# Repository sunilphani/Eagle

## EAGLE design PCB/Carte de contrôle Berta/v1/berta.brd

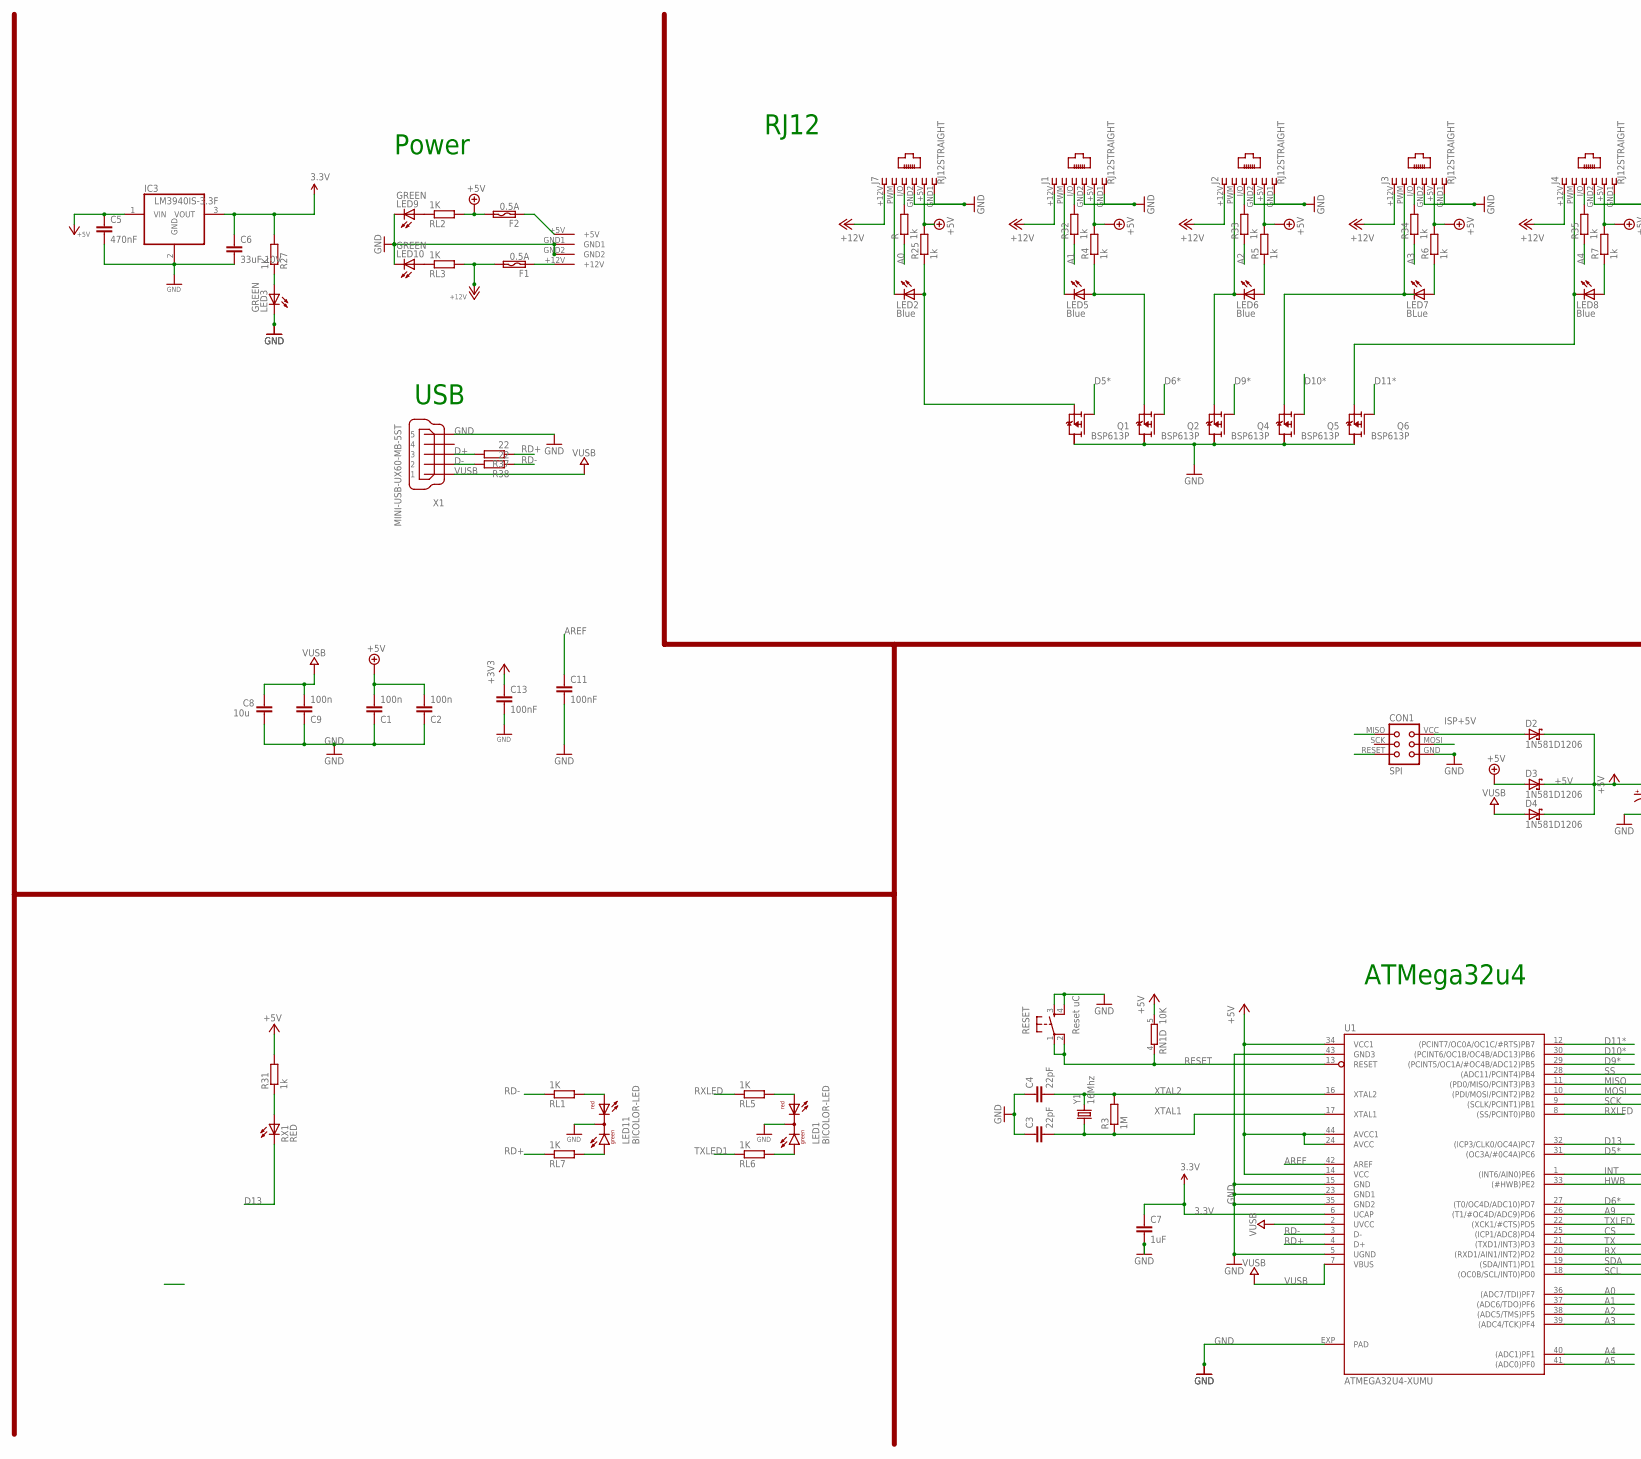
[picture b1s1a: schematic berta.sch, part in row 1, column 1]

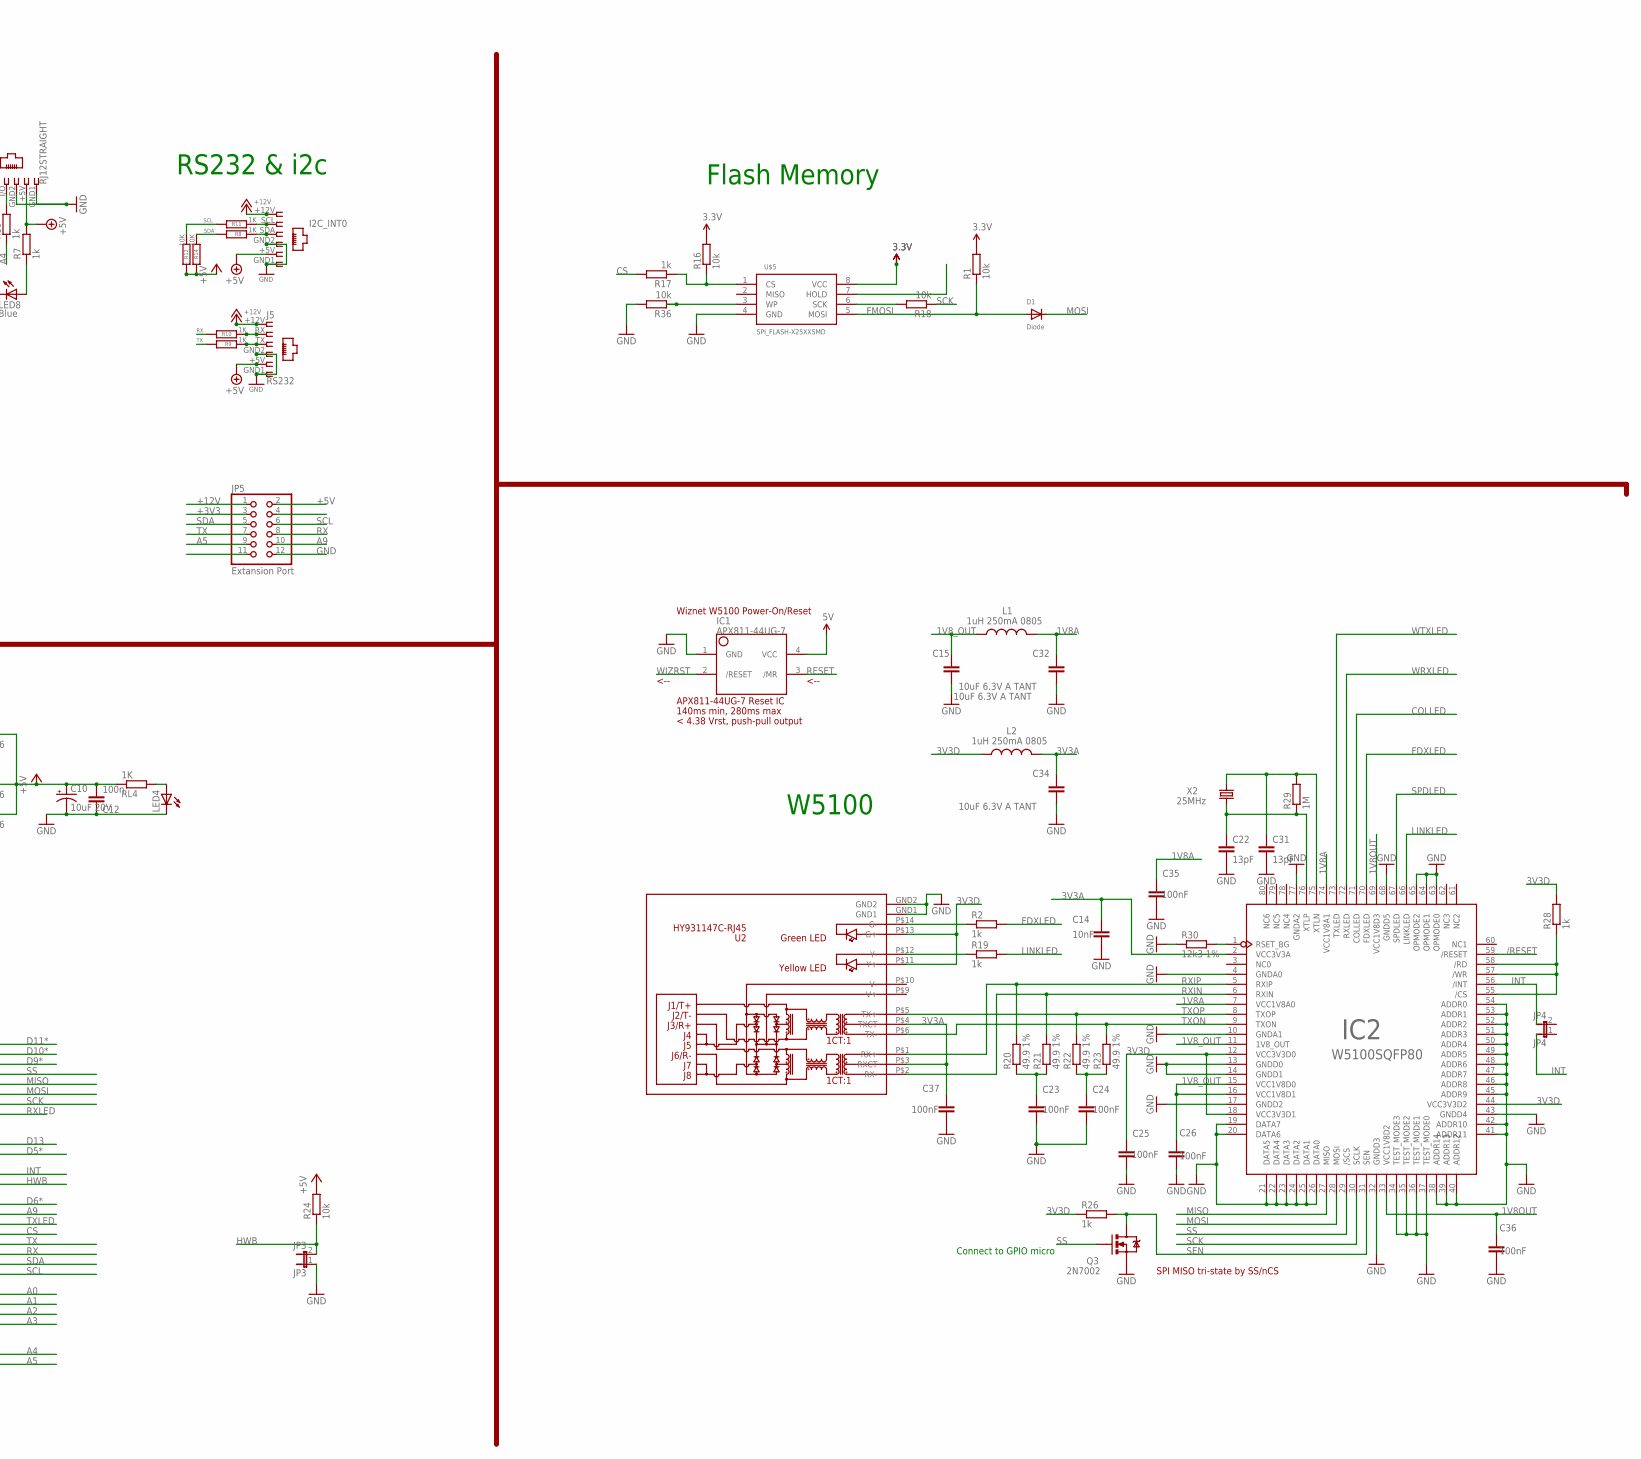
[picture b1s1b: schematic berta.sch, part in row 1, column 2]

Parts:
C1, C2, C9: 100n; C0805
C3, C4: 22pF; C0805
C5: 470nF; C0805
C6: 33uF 10V; C050-045X075
C7: 1uF; C0805
C8: 10u; C0805
C10: 10uF 20V; EIA3216-KIT
C11, C13, C23, C24, C25, C26, C35, C36, C37: 100nF; C0805
C12: 100n; C0603-ROUND
C14: 10nF; C0805
C15, C32, C34: 10uF 6.3V A TANT; C0805
C22, C31: 13pF; C0805
CON1: SPI; TINYISP
D1: Diode; SMADIODE
D2, D3, D4: 1N581D1206; LED-1206
F1, F2: 0.5A; C1812
I2C_INT0: I2C; RJ12-STRAIGHT-I2C
IC1: APX811-44UG-7; SOT143-R
IC2: W5100SQFP80; SQFP80
IC3: LM3940IS-3.3F; DD-3
J1, J2, J3, J4, J7: RJ12STRAIGHT; RJ12-STRAIGHT
J5: RS232; RJ12-STRAIGHT-RS232
JP3: JP3; 1X02
JP4: JP4; 1X02
JP5: Extansion Port; 2X06
L1, L2: 1uH 250mA 0805; L2012C
LED1, LED11: BICOLOR-LED; BICOLOR-3MM
LED2, LED5, LED6, LED8: Blue; SML0805
LED3, LED9, LED10: GREEN; SML0805
LED4: LED3MM
LED7: BLue; SML0805
Q1, Q2, Q4, Q5, Q6: BSP613P; PG-SOT-223
Q3: 2N7002; SOT23-3
R, R4, R5, R6, R7, R17, R25, R32, R33, R34, R35: 1k; M0805
R1, R16, R18, R36: 10k; M0805
R2, R19, R26, R28: 1k; R0805W
R3, R29: 1M; R0805W
R8, R9, R10, R11, R27: 1K; M1206
R12, R14: 10K; M1206
R20, R21, R22, R23: 49.9 1%; R0805W
R24: 10k; R0805W
R30: 12k3 1%; R0805W
R31: 1k; R0805
R37, R38: 22; M1206
RESET: Reset uC; TACTILE_SWITCH_SMD
RL1, RL4, RL5, RL6, RL7: 1K; M1206
RL2, RL3: 1K; R0805W
RN1: 10K; CAY16
RX1: RED; SML0805
U1: ATMEGA32U4-XUMU; QFN44ML7X7
U2: HY931147C-RJ45; HY931147C
U$5: SPI_FLASH-X25XXSMD; SO08
U$6: KPJX-4S-S
X1: MINI-USB-UX60-MB-5ST; UX60-MB-5ST
X2: 25MHz; HC49U-V
Y1: 16Mhz; HC49US

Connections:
1V8A: C32.1, C35.1, IC2.7 (VCC1V8A0), IC2.74 (VCC1V8A1), L1.2
1V8OUT: C36.1, IC2.33 (VCC1V8D2), IC2.69 (VCC1V8D3)
1V8_OUT: C15.1, C26.1, IC2.11 (1V8_OUT), IC2.15 (VCC1V8D0), IC2.16 (VCC1V8D1), L1.1
3.3V: C6.1, C7.1, IC3.3 (VOUT), R1.2, R16.2, R27.2, U1.6 (UCAP), U$5.8 (VCC)
3V3A: C14.1, C34.1, C37.1, IC2.2 (VCC3V3A), L2.2, U2.P$3 (RXCT), U2.P$4 (TXCT)
3V3D: C25.1, IC2.12 (VCC3V3D0), IC2.18 (VCC3V3D1), IC2.44 (VCC3V3D2), L2.1, R26.1, R28.2, U2.P$11 (Y+), U2.P$13 (G+)
5V: IC1.4 (VCC)
+3V3: C13.1
+5V: C1.2, C2.2, C5.1, C10.A (+), C12.2, D2.C, D3.A, D3.C, D4.C, F2.2, I2C_INT0.+5V (5), IC3.1 (VIN), J1.+5V (5), J2.+5V (5), J3.+5V (5), J4.+5V (5), J5.+5V (5), J7.+5V (5), JP5.2, R4.2, R5.2, R6.2, R7.2, R12.2, R14.2, R24.2, R25.2, R31.2, RL2.2, RL4.1, RN1.5 (2), U1.14 (VCC), U1.24 (AVCC), U1.34 (VCC1), U1.44 (AVCC1)
+12V: F1.2, I2C_INT0.+12V (1), J1.+12V (1), J2.+12V (1), J3.+12V (1), J4.+12V (1), J5.+12V (1), J7.+12V (1), RL3.2
/RESET: IC2.59 (/RESET)
A0: R.1, U1.36 ((ADC7/TDI)PF7)
A1: R32.1, U1.37 ((ADC6/TDO)PF6)
A2: R33.1, U1.38 ((ADC5/TMS)PF5)
A3: R34.1, U1.39 ((ADC4/TCK)PF4)
A4: R35.1, U1.40 ((ADC1)PF1)
A5: JP5.9, U1.41 ((ADC0)PF0)
A9: JP5.10, U1.26 ((T1/#OC4D/ADC9)PD6)
AREF: C11.1, U1.42 (AREF)
COLLED: IC2.71 (COLLED)
CS: R17.2, U1.25 ((ICP1/ADC8)PD4)
D2B4: I2C_INT0.SDA (3), R8.1
D2B5: J5.TX (3), R9.1
D5*: Q1.1 (G), U1.31 ((OC3A/#0C4A)PC6)
D6*: Q2.1 (G), U1.27 ((T0/OC4D/ADC10)PD7)
D9*: Q4.1 (G), U1.29 ((PCINT5/OC1A/#OC4B/ADC12)PB5)
D10*: Q5.1 (G), U1.30 ((PCINT6/OC1B/OC4B/ADC13)PB6)
D11*: Q6.1 (G), U1.12 ((PCINT7/OC0A/OC1C/#RTS)PB7)
D13: RX1.C, U1.32 ((ICP3/CLK0/OC4A)PC7)
D+: R37.2, X1.3
D-: R38.2, X1.2
FDXLED: IC2.70 (FDXLED), R2.2
FMOSI: D1.A, R1.1, U$5.5 (MOSI)
GND: C1.1, C2.1, C3.1, C4.1, C5.2, C6.2, C7.2, C8.2, C9.1, C10.C (-), C11.2, C12.1, C13.2, C14.2, C15.2, C22.2, C23.2, C24.2, C25.2, C26.2, C31.2, C32.2, C34.2, C35.2, C36.2, C37.2, CON1.GND, I2C_INT0.GND1 (6), I2C_INT0.GND2 (4), IC1.1 (GND), IC2.4 (GNDA0), IC2.10 (GNDA1), IC2.13 (GNDD0), IC2.14 (GNDD1), IC2.17 (GNDD2), IC2.19 (DATA7), IC2.20 (DATA6), IC2.21 (DATA5), IC2.22 (DATA4), IC2.23 (DATA3), IC2.24 (DATA2), IC2.25 (DATA1), IC2.26 (DATA0), IC2.32 (GNDD3), IC2.34 (TEST_MODE3), IC2.35 (TEST_MODE2), IC2.36 (TEST_MODE1), IC2.37 (TEST_MODE0), IC2.38 (ADDR14), IC2.39 (ADDR13), IC2.40 (ADDR12), IC2.41 (ADDR11), IC2.42 (ADDR10), IC2.43 (GNDD4), IC2.45 (ADDR9), IC2.46 (ADDR8), IC2.47 (ADDR7), IC2.48 (ADDR6), IC2.49 (ADDR5), IC2.50 (ADDR4), IC2.51 (ADDR3), IC2.52 (ADDR2), IC2.53 (ADDR1), IC2.54 (ADDR0), IC2.63 (OPMODE0), IC2.64 (OPMODE1), IC2.65 (OPMODE2), IC2.68 (GNDD5), IC2.77 (GNDA2), IC3.2 (GND), J1.GND1 (6), J1.GND2 (4), J2.GND1 (6), J2.GND2 (4), J3.GND1 (6), J3.GND2 (4), J4.GND1 (6), J4.GND2 (4), J5.GND1 (6), J5.GND2 (4), J7.GND1 (6), J7.GND2 (4), JP3.1, JP5.12, LED1.2 (C), LED3.C, LED4.K (C), LED9.C, LED10.C, LED11.2 (C), Q1.2 (D), Q2.2 (D), Q3.2 (S), Q4.2 (D), Q5.2 (D), Q6.2 (D), R30.1, R36.2, RESET.3, RESET.4, U1.5 (UGND), U1.15 (GND), U1.23 (GND1), U1.35 (GND2), U1.43 (GND3), U1.EXP (PAD), U2.GND1, U2.GND2, U$5.4 (GND), U$6.GND1, U$6.GND2, X1.5
HWB: JP3.2, R24.1, U1.33 ((#HWB)PE2)
INT: IC2.56 (/INT), U1.1 ((INT6/AIN0)PE6)
ISP+5V: CON1.VCC, D2.A
LINKLED: IC2.66 (LINKLED), R19.2
MISO: CON1.MISO, IC2.27 (MISO), U1.11 ((PD0/MISO/PCINT3)PB3)
MOSI: CON1.MOSI, D1.C, IC2.28 (MOSI), U1.10 ((PDI/MOSI/PCINT2)PB2)
unnamed: J2.PWM (2), LED6.C, Q4.3 (S)
unnamed: J1.I/O (3), R32.2
unnamed: R31.1, RX1.A
unnamed: LED5.A, Q2.3 (S), R4.1
unnamed: J3.PWM (2), LED7.C, Q5.3 (S)
unnamed: J2.I/O (3), R33.2
unnamed: LED11.3 (AR), RL1.2
unnamed: C24.1, R22.1, R23.1
unnamed: R16.1, R17.1, U$5.1 (CS)
unnamed: R36.1, U$5.3 (WP)
unnamed: LED4.A, RL4.2
unnamed: LED1.3 (AR), RL5.2
unnamed: LED11.1 (AG), RL7.2
unnamed: LED1.1 (AG), RL6.2
unnamed: J7.I/O (3), R.2
unnamed: J4.PWM (2), LED8.C, Q6.3 (S)
unnamed: LED3.A, R27.1
unnamed: LED2.A, Q1.3 (S), R25.1
unnamed: LED6.A, R5.1
unnamed: R18.2, U$5.6 (SCK)
unnamed: IC2.55 (/CS), IC2.57 (/WR), IC2.58 (/RD), R28.1
unnamed: J1.PWM (2), LED5.C
unnamed: J3.I/O (3), R34.2
unnamed: LED7.A, R6.1
unnamed: J4.I/O (3), R35.2
unnamed: LED8.A, R7.1
unnamed: J7.PWM (2), LED2.C
unnamed: F2.1, U$6.+5V
unnamed: F1.1, U$6.+12V
unnamed: R2.1, U2.P$14 (G-)
unnamed: J5.RX (2), R10.1
unnamed: I2C_INT0.SCL (2), R11.1
unnamed: LED10.A, RL3.1
unnamed: LED9.A, RL2.1
unnamed: C23.1, R20.1, R21.1
unnamed: IC2.1 (RSET_BG), R30.2
unnamed: R19.1, U2.P$12 (Y-)
RD+: R37.1, RL7.1, U1.4 (D+)
RD-: R38.1, RL1.1, U1.3 (D-)
RESET: CON1.RESET, IC1.3 (/MR), RESET.1, RESET.2, RN1.4 (1), U1.13 (RESET)
RX: JP5.8, R10.2, U1.20 ((RXD1/AIN1/INT2)PD2)
RXIN: IC2.6 (RXIN), R21.2, U2.P$2 (RX-)
RXIP: IC2.5 (RXIP), R20.2, U2.P$1 (RX+)
RXLED: RL5.1, U1.8 ((SS/PCINT0)PB0)
SCK: IC2.30 (SCLK), R18.1, U1.9 ((SCLK/PCINT1)PB1)
SCL: JP5.6, R11.2, R12.1, U1.18 ((OC0B/SCL/INT0)PD0)
SDA: JP5.5, R8.2, R14.1, U1.19 ((SDA/INT1)PD1)
SEN: IC2.31 (SEN), Q3.3 (D), R26.2
SPDLED: IC2.67 (SPDLED)
SS: IC2.29 (/SCS), Q3.1 (G), U1.28 ((ADC11/PCINT4)PB4)
TX: JP5.7, R9.2, U1.21 ((TXD1/INT3)PD3)
TXLED: U1.22 ((XCK1/#CTS)PD5)
TXLED1: RL6.1
TXON: IC2.9 (TXON), R23.2, U2.P$6 (TX-)
TXOP: IC2.8 (TXOP), R22.2, U2.P$5 (TX+)
VUSB: C8.1, C9.2, D4.A, U1.2 (UVCC), U1.7 (VBUS), X1.1
WIZRST: IC1.2 (/RESET)
WRXLED: IC2.72 (RXLED)
WTXLED: IC2.73 (TXLED)
XTAL1: C3.2, R3.1, U1.17 (XTAL1), Y1.1
XTAL2: C4.2, R3.2, U1.16 (XTAL2), Y1.2
XTLN: C31.1, IC2.75 (XTLN), R29.2, X2.2
XTLP: C22.1, IC2.76 (XTLP), R29.1, X2.1

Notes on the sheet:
Flash Memory
RJ12
ATMega32u4
W5100
USB
Power
RS232 & i2c
SPI MISO tri-state by SS/nCS
Connect to GPIO micro
APX811-44UG-7 Reset IC
140ms min, 280ms max
Wiznet W5100 Power-On/Reset
< 4.38 Vrst, push-pull output
<--

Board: 2 copper layers, 119 parts (0 on the bottom side), 93 nets, no tracks yet.

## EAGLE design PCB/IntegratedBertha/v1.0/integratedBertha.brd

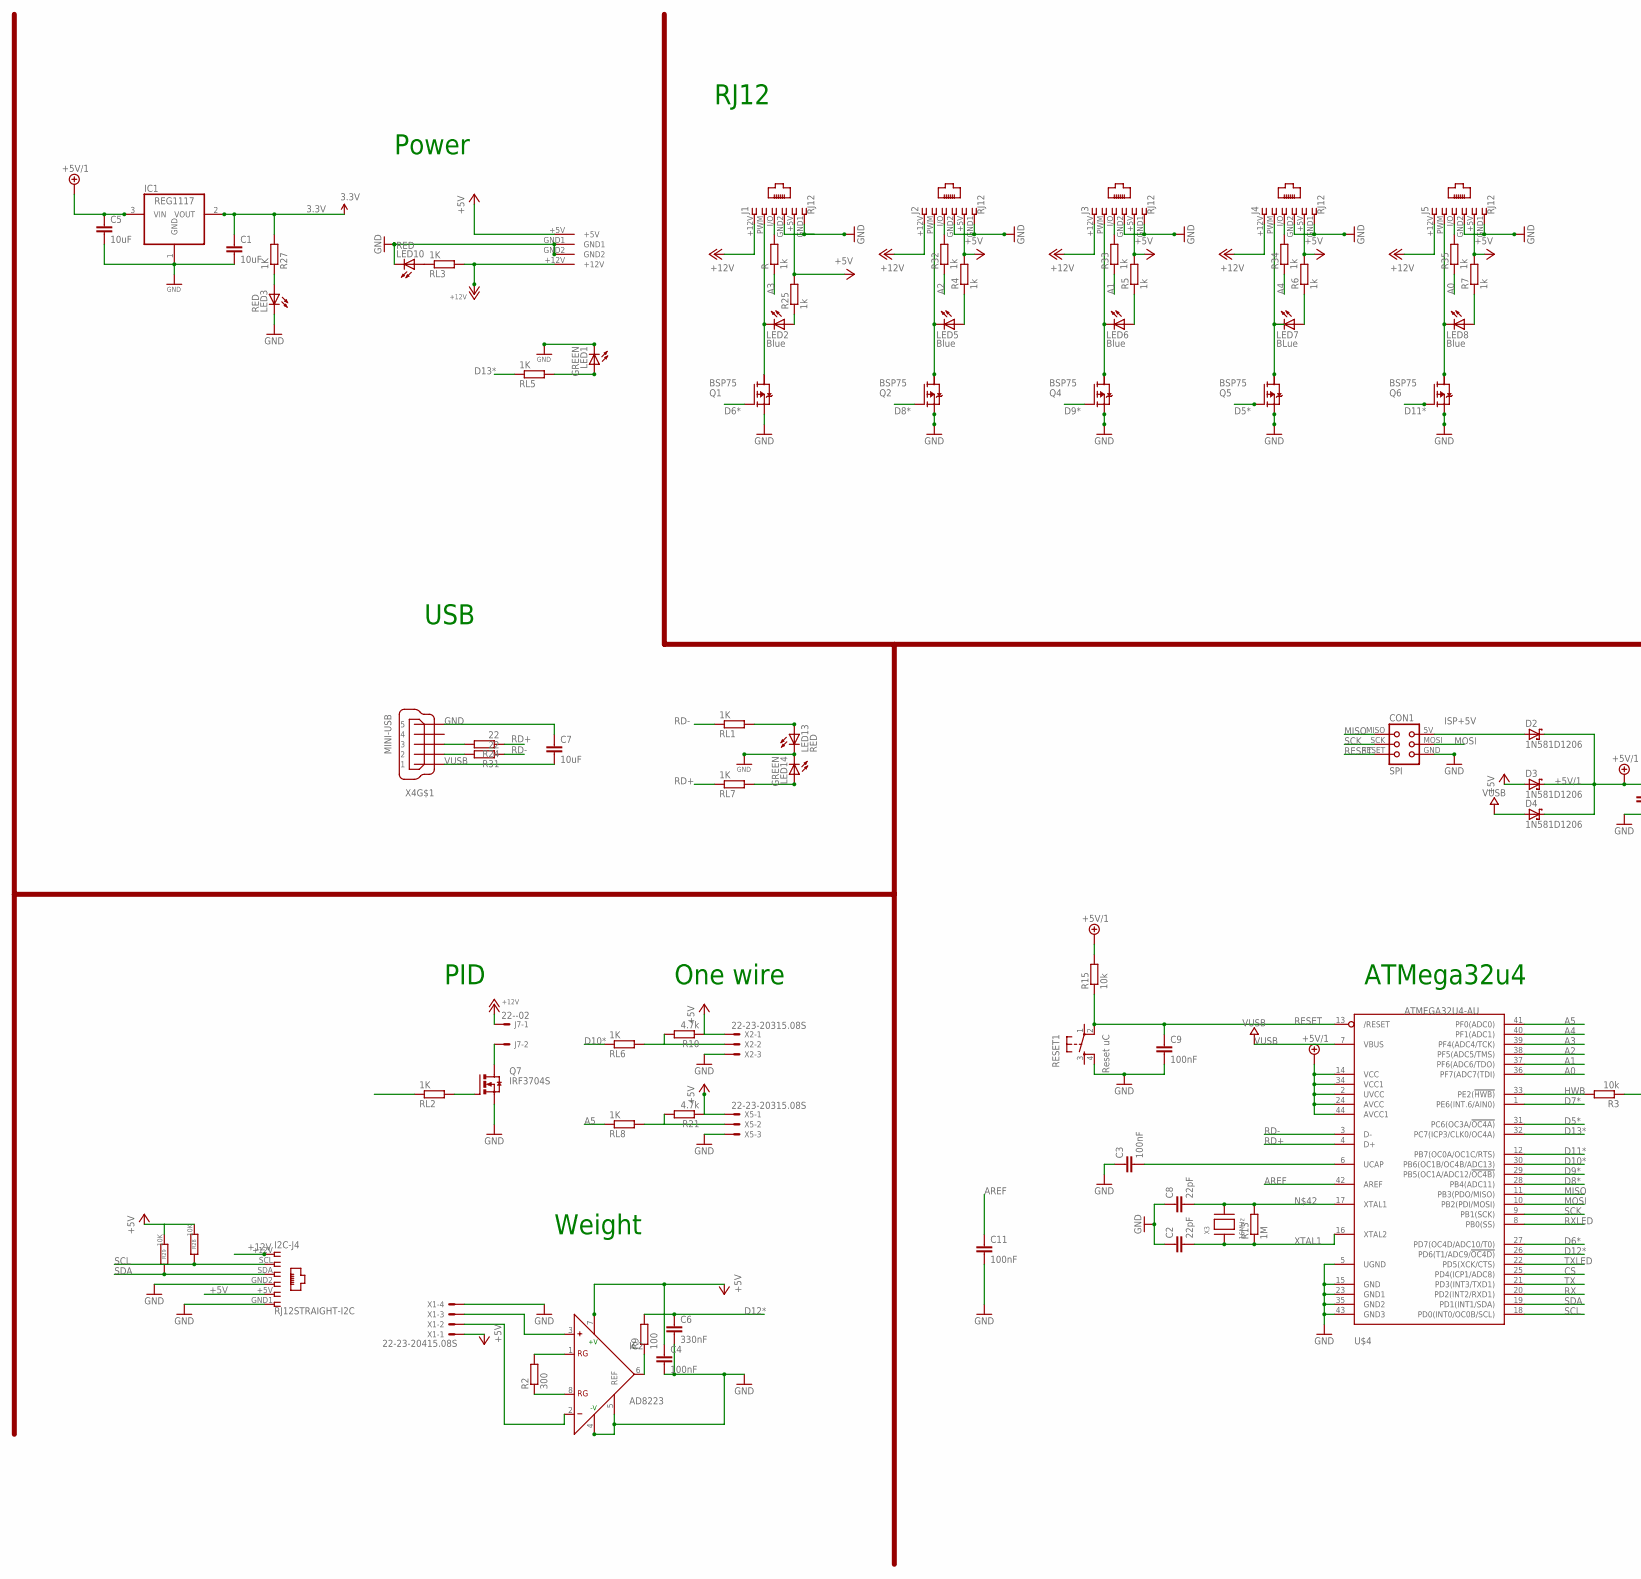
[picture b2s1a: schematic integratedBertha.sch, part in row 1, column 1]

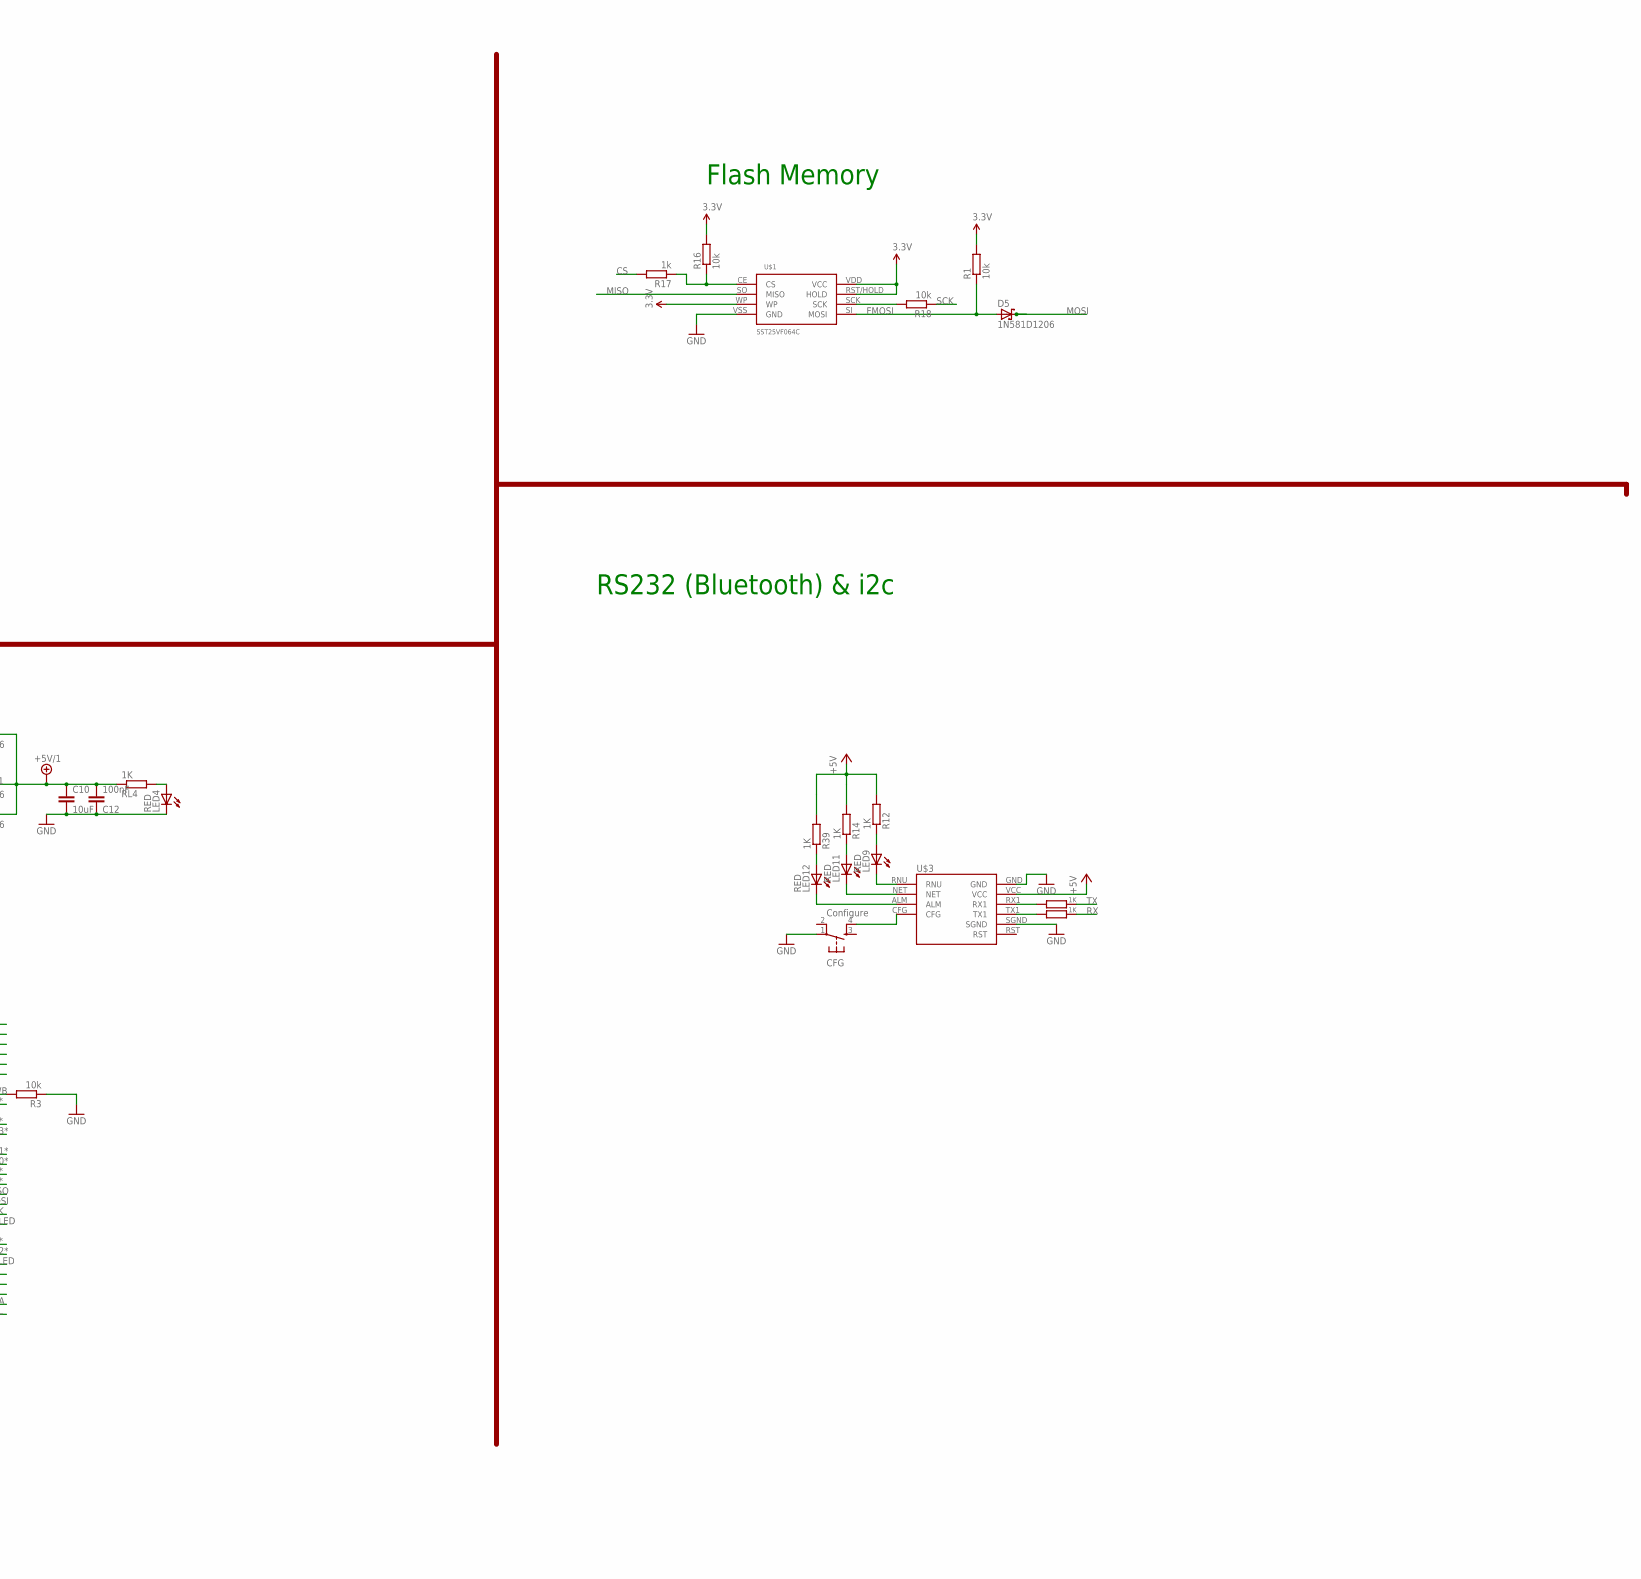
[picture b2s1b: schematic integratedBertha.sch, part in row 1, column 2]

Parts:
C1, C5, C7, C10: 10uF; C1206
C2, C8: 22pF; C1206
C3, C4, C9, C11, C12: 100nF; C1206
C6: 330nF; C1206
CFG: Configure; TACTILE_SWITCH_SMD
CON1: SPI; TC2030-MCP-NL
D2, D3, D4, D5: 1N581D1206; LED-1206
I2C-J4: RJ12STRAIGHT-I2C; RJ12-STRAIGHT-I2C
IC1: REG1117; SOT223
IC2: AD8223; SO8
J1, J2, J3, J4, J5: RJ12; RJ12-STRAIGHT
J7: 22--02; 2-PIN-5.08S
LED1, LED14: GREEN; CHIPLED_1206
LED2, LED5, LED6, LED8: Blue; CHIPLED_1206
LED3, LED4, LED9, LED10, LED11, LED12, LED13: RED; CHIPLED_1206
LED7: BLue; CHIPLED_1206
Q1, Q2, Q4, Q5, Q6: BSP75; PG-SOT-223
Q7: IRF3704S; D2PACK
R, R4, R5, R6, R7, R17, R25, R32, R33, R34, R35: 1k; R0805
R1, R16, R18: 10k; R0805
R2: 300; R1206
R3, R15: 10k; M0805
R8, R11, R12, R14, R27, R39: 1K; R0805
R9: 100; R1206
R10, R21: 4.7k; R1206
R13: 1M; R1206
R24, R31: 22; M1206
R28, R29: 10K; M0805
RESET1: Reset uC; TACTILE_SWITCH_SMD
RL1, RL2, RL3, RL4, RL5, RL6, RL7, RL8: 1K; R0805
U$1: SST25VF064C; SOIC_8-LEAD
U$3: SZ05-ZIGBEE
U$4: ATMEGA32U4-AU; TQFP44
U$6: KPJX-4S-S
X1: 22-23-20415.08S; 4-PIN-5.08S
X2, X5: 22-23-20315.08S; 3-PIN-5.08S
X3: 16MHz; NX6035
X4: MINI-USB; 32005-201

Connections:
3.3V: C1.1, IC1.2 (VOUT), R1.2, R16.2, R27.2, U$1.RST/HOLD (HOLD), U$1.VDD (VCC), U$1.WP
+5V: C4.1, D3.A, I2C-J4.+5V (5), IC2.7 (+V), J1.+5V (5), J2.+5V (5), J3.+5V (5), J4.+5V (5), J5.+5V (5), R4.2, R5.2, R6.2, R7.2, R10.1, R12.2, R14.2, R21.1, R25.2, R28.1, R29.1, R39.2, U$3.VCC, U$6.+5V, X1.1, X2.1, X5.1
+5V/1: C5.1, C10.1, C12.2, D2.C, D3.C, D4.C, IC1.3 (VIN), R15.2, RL4.1, U$4.2 (UVCC), U$4.14 (VCC), U$4.24 (AVCC), U$4.34 (VCC1), U$4.44 (AVCC1)
+12V: I2C-J4.+12V (1), J1.+12V (1), J2.+12V (1), J3.+12V (1), J4.+12V (1), J5.+12V (1), J7.1, RL3.2, U$6.+12V
A0: R35.1, U$4.36 (PF7(ADC7(TDI))
A1: R33.1, U$4.37 (PF6(ADC6/TDO))
A2: R32.1, U$4.38 (PF5(ADC5/TMS))
A3: R.1, U$4.39 (PF4(ADC4/TCK))
A4: R34.1, U$4.40 (PF1(ADC1))
A5: RL8.1, U$4.41 (PF0(ADC0))
AREF: C11.1, U$4.42 (AREF)
CS: R17.2, U$4.25 (PD4(ICP1/ADC8))
D5*: Q5.1 (G), U$4.31 (PC6(OC3A/!OC4A))
D6*: Q1.1 (G), U$4.27 (PD7(OC4D/ADC10/T0))
D7*: RL2.1, U$4.1 (PE6(INT.6/AIN0))
D8*: Q2.1 (G), U$4.28 (PB4(ADC11))
D9*: Q4.1 (G), U$4.29 (PB5(OC1A/ADC12/!OC4B))
D10*: RL6.1, U$4.30 (PB6(OC1B/OC4B/ADC13))
D11*: Q6.1 (G), U$4.12 (PB7(OC0A/OC1C/RTS))
D12*: C6.1, R9.2, U$4.26 (PD6(T1/ADC9/!OC4D))
D13*: RL5.1, U$4.32 (PC7(ICP3/CLK0/OC4A))
D+USB: R24.2, X4.3
D-USB: R31.2, X4.2
DIFF+: IC2.3 (+), X1.3
DIFF-: IC2.2 (-), X1.2
FMOSI: D5.A, R1.1, U$1.SI (MOSI)
GND: C1.2, C2.1, C3.1, C4.2, C5.2, C6.2, C7.1, C8.1, C9.2, C10.2, C11.2, C12.1, CFG.1, CON1.GND, I2C-J4.GND1 (6), I2C-J4.GND2 (4), IC1.1 (GND), IC2.4 (-V), IC2.5 (REF), J1.GND1 (6), J1.GND2 (4), J2.GND1 (6), J2.GND2 (4), J3.GND1 (6), J3.GND2 (4), J4.GND1 (6), J4.GND2 (4), J5.GND1 (6), J5.GND2 (4), LED1.C, LED3.C, LED4.C, LED10.C, LED13.C, LED14.C, Q1.3 (S), Q2.3 (S), Q4.3 (S), Q5.3 (S), Q6.3 (S), Q7.3 (S), R3.1, RESET1.4, U$1.VSS (GND), U$3.GND, U$3.SGND, U$4.5 (UGND), U$4.15 (GND), U$4.23 (GND1), U$4.35 (GND2), U$4.43 (GND3), U$6.GND1, U$6.GND2, X1.4, X2.3, X4.5, X5.3
GND1: LED9.C, U$3.RNU
GND2: LED11.C, U$3.NET
GND3: LED12.C, U$3.ALM
HWB: R3.2, U$4.33 (PE2(!HWB))
ISP+5V: CON1.5V (VCC), D2.A
MISO: CON1.MISO, U$1.SO (MISO), U$4.11 (PB3(PDO/MISO))
MOSI: CON1.MOSI, D5.C, U$4.10 (PB2(PDI/MOSI))
unnamed: J3.PWM (2), LED6.C, Q4.2 (D)
unnamed: J2.I/O (3), R32.2
unnamed: LED1.A, RL5.2
unnamed: LED5.A, R4.1
unnamed: J4.PWM (2), LED7.C, Q5.2 (D)
unnamed: Q7.1 (G), RL2.2
unnamed: J3.I/O (3), R33.2
unnamed: LED13.A, RL1.2
unnamed: R21.2, RL8.2, X5.2
unnamed: R16.1, R17.1, U$1.CE (CS)
unnamed: R11.2, U$3.RX1
unnamed: LED4.A, RL4.2
unnamed: IC2.1 (RG), R2.2
unnamed: LED14.A, RL7.2
unnamed: IC2.8 (RG), R2.1
unnamed: C3.2, U$4.6 (UCAP)
unnamed: LED2.A, R25.1
unnamed: J1.I/O (3), R.2
unnamed: J5.PWM (2), LED8.C, Q6.2 (D)
unnamed: LED3.A, R27.1
unnamed: R10.2, RL6.2, X2.2
unnamed: LED6.A, R5.1
unnamed: R18.2, U$1.SCK
unnamed: R8.2, U$3.TX1
unnamed: LED9.A, R12.1
unnamed: LED11.A, R14.1
unnamed: LED12.A, R39.1
unnamed: J2.PWM (2), LED5.C, Q2.2 (D)
unnamed: J4.I/O (3), R34.2
unnamed: LED7.A, R6.1
unnamed: J5.I/O (3), R35.2
unnamed: LED8.A, R7.1
unnamed: J1.PWM (2), LED2.C, Q1.2 (D)
unnamed: CFG.4, U$3.CFG
unnamed: J7.2, Q7.2 (D)
unnamed: IC2.6 (OUT), R9.1
unnamed: C8.2, R13.2, U$4.17 (XTAL1), X3.P$2
unnamed: LED10.A, RL3.1
RD+: R24.1, RL7.1, U$4.4 (D+)
RD-: R31.1, RL1.1, U$4.3 (D-)
RESET: C9.1, CON1.RESET, R15.1, RESET1.2, U$4.13 (/RESET)
RX: R8.1, U$4.20 (PD2(INT2/RXD1))
RXLED: U$4.8 (PB0(SS))
SCK: CON1.SCK, R18.1, U$4.9 (PB1(SCK))
SCL: I2C-J4.SCL (2), R28.2, U$4.18 (PD0(INT0/OC0B/SCL))
SDA: I2C-J4.SDA (3), R29.2, U$4.19 (PD1(INT1/SDA))
TX: R11.1, U$4.21 (PD3(INT3/TXD1))
TXLED: U$4.22 (PD5(XCK/CTS))
VUSB: C7.2, D4.A, U$4.7 (VBUS), X4.1
XTAL1: C2.2, R13.1, U$4.16 (XTAL2), X3.P$1

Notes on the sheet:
Flash Memory
RJ12
ATMega32u4
USB
Power
RS232 (Bluetooth) & i2c
PID
One wire
Weight

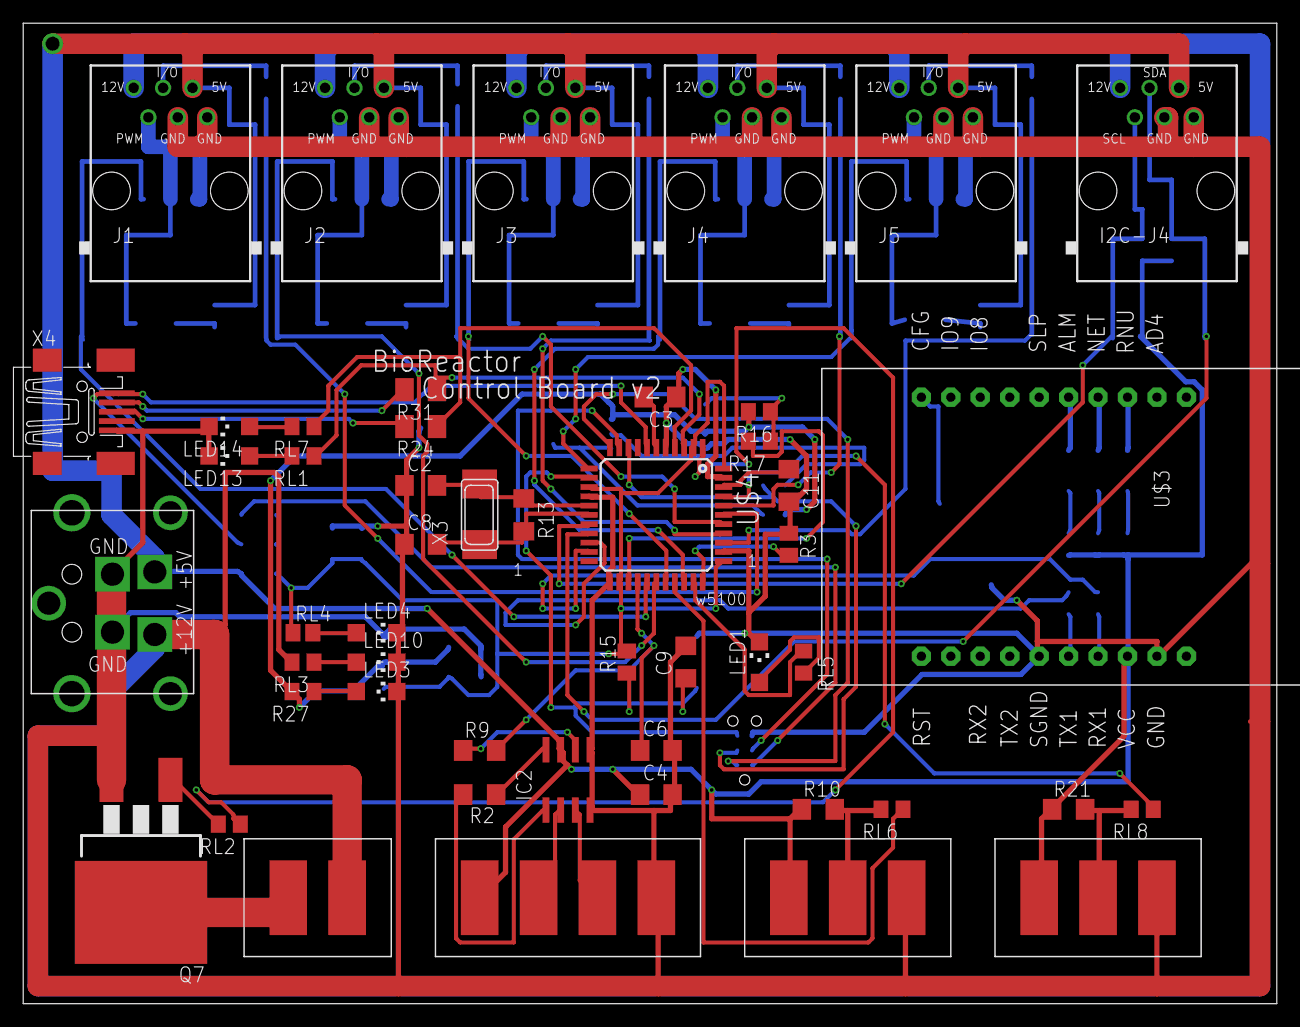
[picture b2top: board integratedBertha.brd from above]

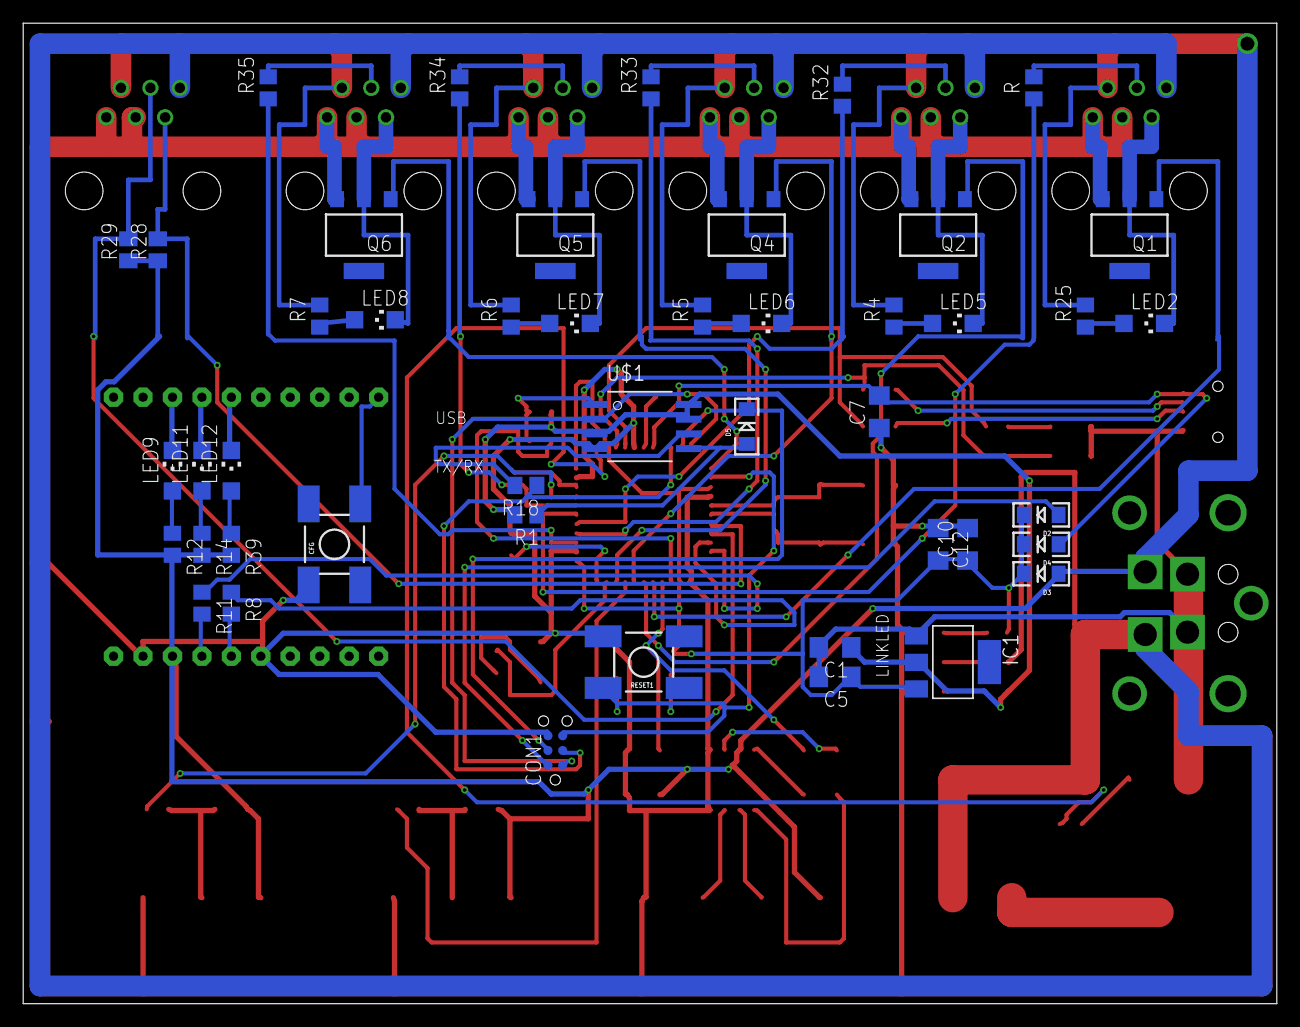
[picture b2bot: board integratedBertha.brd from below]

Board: 2 copper layers, 108.1 x 84.6 mm, 96 parts (46 on the bottom side), 82 nets.

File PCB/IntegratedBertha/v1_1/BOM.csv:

"Qty";"Value";"Device";"Package";"Parts";"Description";"";
"1";"100";"R-EU_R1206";"R1206";"R9";"RESISTOR, European symbol";"";
"7";"100nF";"C-EUC1206";"C1206";"C3, C4, C9, C11, C12, C14, C15";"CAPACITOR, European symbol";"";
"1";"100uF";"C-EUC1206";"C1206";"C16";"CAPACITOR, European symbol";"";
"2";"10K";"R-EU_M0805";"M0805";"R28, R29";"RESISTOR, European symbol";"";
"2";"10k";"R-EU_M0805";"M0805";"R3, R15";"RESISTOR, European symbol";"";
"3";"10k";"R-EU_R0805";"R0805";"R1, R16, R18";"RESISTOR, European symbol";"";
"4";"10uF";"C-EUC1206";"C1206";"C1, C5, C7, C10";"CAPACITOR, European symbol";"";
"1";"10uH";"L-USL2012C";"L2012C";"L1";"INDUCTOR, American symbol";"";
"1";"16MHz";"XTALNX6035";"NX6035";"X3";"Low cost SMT crystals, no capacitors included";"";
"12";"1K";"R-EU_R0805";"R0805";"R8, R11, R12, R14, R27, R39, RL2, RL3, RL4, RL5, RL6, RL8";"RESISTOR, European symbol";"";
"1";"1M";"R-EU_R1206";"R1206";"R13";"RESISTOR, European symbol";"";
"4";"1N581D1206";"1N581D1206";"LED-1206";"D2, D3, D4, D5";"1.0A SCHOTTKY BARRIER RECTIFIER";"";
"11";"1k";"R-EU_R0805";"R0805";"R, R4, R5, R6, R7, R17, R25, R32, R33, R34, R35";"RESISTOR, European symbol";"";
"2";"22";"R-EU_M1206";"M1206";"R24, R31";"RESISTOR, European symbol";"";
"1";"22--02";"22--02";"2-PIN-5.08S";"J7";"CONNECTOR";"";
"2";"22-23-20315.08S";"22-23-20315.08S";"3-PIN-5.08S";"X2, X5";".100" (2.54mm) Center Header - 3 Pin";"";
"1";"22-23-20415.08S";"22-23-20415.08S";"4-PIN-5.08S";"X1";".100" (2.54mm) Center Header - 4 Pin";"";
"2";"22pF";"C-EUC1206";"C1206";"C2, C8";"CAPACITOR, European symbol";"";
"1";"300";"R-EU_R1206";"R1206";"R2";"RESISTOR, European symbol";"";
"1";"330nF";"C-EUC1206";"C1206";"C6";"CAPACITOR, European symbol";"";
"2";"4.7k";"R-EU_R1206";"R1206";"R10, R21";"RESISTOR, European symbol";"";
"1";"4.7uF";"C-EUC1206";"C1206";"C13";"CAPACITOR, European symbol";"";
"2";"49.9";"R-EU_R1206";"R1206";"R19, R20";"RESISTOR, European symbol";"";
"1";"AD8223";"AD620R";"SO8";"IC2";"Low Cost, Low Power, Instrumentation Amplifier";"";
"1";"ATMEGA32U4";"ATMEGA32U4-AU";"TQFP44";"U$4";"http://www.ladyada.net/library/eagle";"";
"1";"BLue";"LEDCHIPLED_1206";"CHIPLED_1206";"LED7";"LED";"";
"5";"BSP75";"BSP613P";"PG-SOT-223";"Q1, Q2, Q4, Q5, Q6";"SIPMOS (R) Small-Signal-Transistor P-Channel (2 Drain)";"";
"4";"Blue";"LEDCHIPLED_1206";"CHIPLED_1206";"LED2, LED5, LED6, LED8";"LED";"";
"1";"Configure";"TAC_SWITCHSMD";"TACTILE_SWITCH_SMD";"CFG";"Momentary Switch";"";
"1";"GREEN";"LEDCHIPLED_1206";"CHIPLED_1206";"BLINK";"LED";"";
"1";"IRF3704S";"IRF3704S";"D2PACK";"Q7";"SMPS MOSFET";"";
"1";"KPJX-4S-S";"KPJX-4S-S";"KPJX-4S-S";"U$6";"";"";
"1";"MINI-USB";"MINI-USB-SCHIELD-32005-201";"32005-201";"X4";"MINI USB-B Conector";"";
"6";"RED";"LEDCHIPLED_1206";"CHIPLED_1206";"3.3V-OK, 5V-OK, 12V-OK, LED9, LED11, LED12";"LED";"";
"1";"REG1117";"REG1117";"SOT223";"IC1";"800mA and 1A Low Dropout (LDO) Positive Regulator";"";
"5";"RJ12";"RJ12STRAIGHT";"RJ12-STRAIGHT";"I/O1, I/O2, I/O3, I/O4, I/O5";"CORCOM Modular RJ Jacks No Shield";"";
"1";"RJ12STRAIGHT-I2C";"RJ12STRAIGHT-I2C";"RJ12-STRAIGHT-I2C";"I2C";"CORCOM Modular RJ Jacks No Shield";"";
"1";"Reset uC";"TAC_SWITCHSMD";"TACTILE_SWITCH_SMD";"RESET1";"Momentary Switch";"";
"1";"SPI";"TINYISPT";"TC2030-MCP-NL";"CON1";"CONNECTOR";"";
"1";"SST25VF064C";"SST25VF064C";"SOIC_8-LEAD";"U$1";"";"";
"1";"STARGND";"STARGND";"STAR";"U$2";"";"";
"1";"SZ05-ZIGBEE";"SZ05-ZIGBEETHROUGHHOLE";"SZ05-ZIGBEE4";"U$3";"";"";

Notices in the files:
parts and their libraries:
SparkFun: Licensing: CC v3.0 Share-Alike You are welcome to use this library for commercial purposes.
lpatiny: ©2009 ROFA.cz - modified and updated by Robert Darlington ‹rdarlington@gmail.com›
